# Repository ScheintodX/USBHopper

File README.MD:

#USB-Hopper

*The swiss army knife for working with microcontrollers*

##Features

* Serial interface using a FT232R
* 3 Voltages Powersupply using efficient DC-DC Buck converters:
** 5V directly from USB Bus (500mA)
** 3.3V 600mA
** 1.8V 600mA
** USB suspend supported
** not usable for heating coffee, sorry!
* USB-A Connector (no stupid cables)
* IO voltages selectable via jumper
* Sense / PWR / RX / TX LEDs
* All 4 Leds are multipurpose usable as poor mans osciloscope
* RS485 on board
* multiple comfortable headers
* cool pcb layout with sublimal messages (yea, you can call 2pt fonts sublimal ;)

##Usage Scenarios

* directly connect ESP8266 mcus to power and program them
* connect arduino boards and use the leds to show pins switching
* use rs485 to debug housebus installations or transmit data over long distances

##Errata

* RS485 termination is wrong

##Missing Features

* Additional circuity for programming esp8266 supporting RESET
* Use KiCAD instead of Eagle
* Better isolation of Sense pins
* JTAG is not working well with FT232R and so didn't manage to get in.

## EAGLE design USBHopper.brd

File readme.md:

#USB-Hopper

*The swiss army knife for working with microcontrollers*

##Features

* Serial interface using a FT232R
* 3 Voltages Powersupply using efficient DC-DC Buck converters:
** 5V directly from USB Bus (500mA)
** 3.3V 600mA
** 1.8V 600mA
** USB suspend supported
** not usable for heating coffee, sorry!
* USB-A Connector (no stupid cables)
* IO voltages selectable via jumper
* Sense / PWR / RX / TX LEDs
* All 4 Leds are multipurpose usable as poor mans osciloscope
* RS485 on board
* multiple comfortable headers
* cool pcb layout with sublimal messages (yea, you can call 2pt fonts sublimal ;)
* different assembly options using less voltages or other voltages, 

##Usage Scenarios

* directly connect ESP8266 mcus to power and program them
* connect arduino boards and use the leds to show pins switching
* use rs485 to debug housebus installations or transmit data over long distances

##Errata

** RN4604 IC must be mounted 180° rotated! **

* RS485 termination is wrong

* USB-Power supply may need less parts

##Missing Features

* Additional circuity for programming esp8266 supporting RESET
* Use KiCAD instead of Eagle
* Better isolation of Sense pins
* JTAG is not working well with FT232R and so didn't manage to get in.
* Make RE/DI controllable by FTDI pins
* Put RTS/DTR on pads (not only pins because they are usefull for esp programming)
* Make external power switchable via some signal lines / jumpers / both

#Files:

* *.brd, *.sch: eagle board and schema files
* *.BOM: Bill of Materials (text)
* parts.ods: Unfinished spreadsheet with incomplete list of parts and where to buy them and what they may have costed a long long time ago.

#Make compile

* Start with the biggest IC: the FTDI chip. There are multiple ways how you can get it on the pcb. In my optinion this is the easiest one: Put as little solder as possible on each pad. Now apply flux from a pen. Place the IC exactly on the pads and using a knife tip on the soldering iron go across the legs. Check e.g. using your mobile and some magnifing app.

* Now solder the small ics like the DC-DC converters, the mosfet and the transistor arrays. Here it works best first putting solder on *one* pad, placing the ic then soldering that one leg. Now the IC can't move anymore and you can solder the other legs easily.

* Then its time for the resistors and capacitors. Apply the same procedure as with the small ICs. I like using my fingernails to hold them while soldering but you can use tweezers, of cause.

* Now put on the remaining stuff. The usb connector and the pin header come last because they go though the pcb so that it can't lay flat anymore which would have been a major anoyance while mounting the other parts.

* finally connect the solder bridges apropriately.

#Brides/Jumpers

A. Main Power Supply jumper:

This one controls the power supply for the ftdi io pins and most of the header pins. It can have 4 settings: 5V, 3.3V FT generated, 3.3V Buck generated and 1.8V. 

B. Power LED Jumper + additional Sense pin

Can be used to disconnect the (blue) power led and use it as additional sense pin.

C. Connect RO / DI Pins of RS485 to Rx/Tx of the FT

D. Sense pin. Controls the (red) sense led.

E. Two more sense pins which can controll the Rx/Tx Leds

F. Select supply voltage to the RS485 Transceiver. Depends on the Transceiver used. Normally 3.3V.

G. Connect DE/RE Pins of the transceiver to Vcc/GND. You normally want to do this.

H. Either connect the Tx/Rx LEDS directly to the FT Led pins (jumper closed) or via transistor to the Tx/Rx Lines (jumper open but transistor arrays on the board.)

K. Not really good termination settings.

# Config

The FT232R has many config options. Use the "FT_Prog" utility to change pin mappings and maximum power rating.

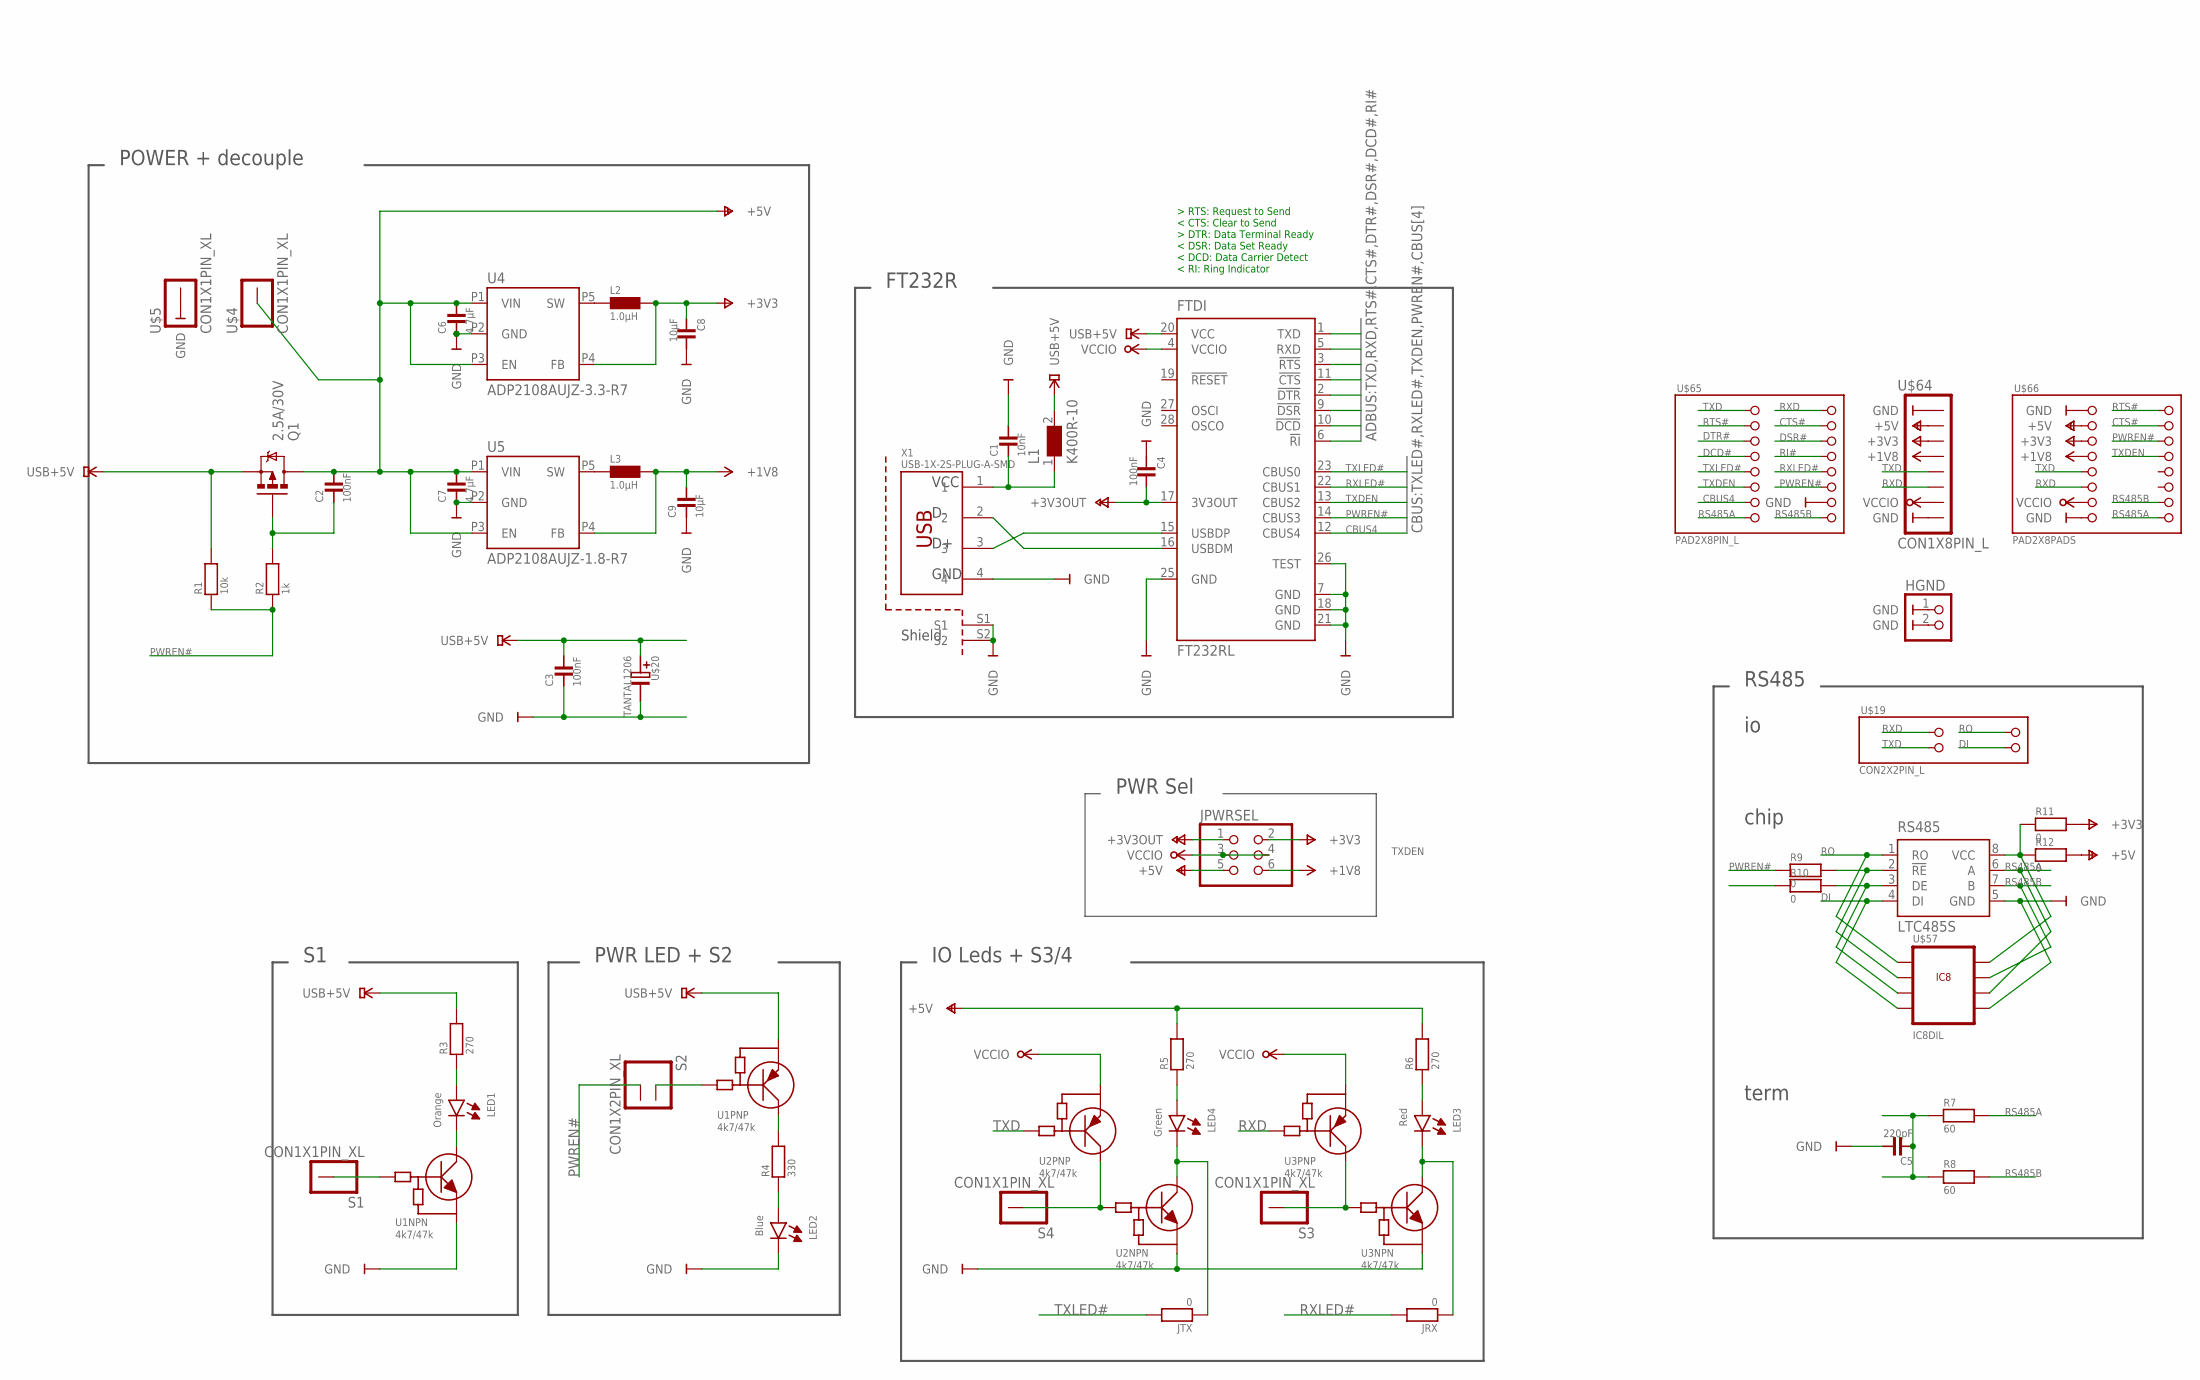
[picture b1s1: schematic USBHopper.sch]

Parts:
C1: 10nF; 0805
C2, C3, C4: 100nF; 0805
C5: 220pF; 0805
C6, C7: 4.7µF; 0805
C8, C9: 10µF; 0805
FTDI: FT232RL; SSOP28_FLO
HGND: PINHD-1X2; 1X02
JPWRSEL: PINHD-2X3; 2X03
JRX: 0; 0805_CONNECT
JTX: 0; 0805_CONNECT
L1: K400R-10; 0805
L2, L3: 1.0µH; 0806
LED1: Orange; KPT-2012-E
LED2: Blue; KPT-2012-E
LED3: Red; KPT-2012-E
LED4: Green; KPT-2012-E
Q1: 2.5A/30V; SOT23-3
R1: 10k; 0805
R2: 1k; 0805
R3, R5, R6: 270; 0805
R4: 330; 0805
R7: 60; 0805
R8: 60; 0805_CONNECT
R9, R10, R11, R12: 0; 0805_CONNECT
RS485: LTC485S; SOIC8
S1, S3, S4: CON1X1PIN_XL; 1X1PINS
S2: CON1X2PIN_XL; 1X2PINS
U1, U2, U3: 4k7/47k; SOT-457
U4: ADP2108AUJZ-3.3-R7; SOT23
U5: ADP2108AUJZ-1.8-R7; SOT23
U$4, U$5: CON1X1PIN_XL; 1X1PINS
U$19: CON2X2PIN_L; 2X2PINS_L
U$20: TANTAL1206; 1206
U$57: IC8DIL; DIL8
U$64: CON1X8PIN_L; 1X8PINS_L
U$65: PAD2X8PIN_L; 2X8PINS_L
U$66: PAD2X8PADS; 2X8PADS
X1: USB-1X-2S-PLUG-A-SMD; USB-PLUG-A-SMD-2S

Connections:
+1V8: C9.P$2, JPWRSEL.6, L3.P$1, U5.P4 (FB), U$64.P$4, U$66.P$7
+3V3: C8.P$1, JPWRSEL.2, L2.P$1, R11.P$2, U4.P4 (FB), U$64.P$3, U$66.P$5
+3V3OUT: C4.P$2, FTDI.17 (3V3OUT), JPWRSEL.1
+5V: C2.P$2, C6.P$2, C7.P$2, JPWRSEL.5, Q1.3 (D), R5.P$2, R6.P$2, R12.P$2, U4.P1 (VIN), U4.P3 (EN), U5.P1 (VIN), U5.P3 (EN), U$4.P$1, U$64.P$2, U$66.P$3
CBUS4: FTDI.12 (CBUS4), U$65.P$13
CTS#: FTDI.11 (!CTS), U$65.P$4, U$66.P$4
DCD#: FTDI.10 (!DCD), U$65.P$7
DE: R10.P$2, RS485.3 (DE), U$57.P$3
DI: RS485.4 (DI), U$19.P$4, U$57.P$4
DSR#: FTDI.9 (!DSR), U$65.P$6
DTR#: FTDI.2 (!DTR), U$65.P$5
GND: C1.P$2, C3.P$1, C4.P$1, C5.P$2, C6.P$1, C7.P$1, C8.P$2, C9.P$1, FTDI.7 (GND), FTDI.18 (GND), FTDI.21 (GND), FTDI.25 (GND), FTDI.26 (TEST), HGND.1, HGND.2, LED2.2, RS485.5 (GND), U1.P$1 (E), U2.P$1 (E), U3.P$1 (E), U4.P2 (GND), U5.P2 (GND), U$5.P$1, U$20.P$2, U$57.P$5, U$64.P$1, U$64.P$8, U$65.P$14, U$66.P$1, U$66.P$15, X1.4, X1.S1, X1.S2
unnamed: LED2.1, R4.P$1
unnamed: LED1.1, R3.P$1
unnamed: C1.P$1, L1.1, X1.1
unnamed: L2.P$2, U4.P5 (SW)
unnamed: JRX.P$1, LED3.2, U3.P$6 (C)
unnamed: L3.P$2, U5.P5 (SW)
unnamed: C5.P$1, R7.P$1, R8.P$1
unnamed: R11.P$1, R12.P$1, RS485.8 (VCC), U$57.P$8
unnamed: JTX.P$1, LED4.2, U2.P$6 (C)
unnamed: LED4.1, R5.P$1
unnamed: LED3.1, R6.P$1
unnamed: R4.P$2, U1.P$3 (C)
unnamed: S2.P$1, U1.P$5 (B)
unnamed: LED1.2, U1.P$6 (C)
PWREN: C2.P$1, Q1.1 (G), R2.P$2
PWREN#: FTDI.14 (CBUS3), R1.P$1, R2.P$1, R9.P$1, S2.P$2, U$65.P$12, U$66.P$6
RE#: R9.P$2, RS485.2 (!RE), U$57.P$2
RI#: FTDI.6 (!RI), U$65.P$8
RO: RS485.1 (RO), U$19.P$2, U$57.P$1
RS485A: R7.P$2, RS485.6 (A), U$57.P$6, U$65.P$15, U$66.P$16
RS485B: R8.P$2, RS485.7 (B), U$57.P$7, U$65.P$16, U$66.P$14
RTS#: FTDI.3 (!RTS), U$65.P$3, U$66.P$2
RXD: FTDI.5 (RXD), U3.P$5 (B), U$19.P$1, U$64.P$6, U$65.P$2, U$66.P$11
RXLED#: FTDI.22 (CBUS1), JRX.P$2, U$65.P$10
SEN3: S4.P$1, U2.P$2 (B), U2.P$3 (C)
SEN4: S3.P$1, U3.P$2 (B), U3.P$3 (C)
SENSE: S1.P$1, U1.P$2 (B)
TXD: FTDI.1 (TXD), U2.P$5 (B), U$19.P$3, U$64.P$5, U$65.P$1, U$66.P$9
TXDEN: FTDI.13 (CBUS2), R10.P$1, U$65.P$11, U$66.P$8
TXLED#: FTDI.23 (CBUS0), JTX.P$2, U$65.P$9
USB+5V: C3.P$2, FTDI.20 (VCC), L1.2, Q1.2 (S), R1.P$2, R3.P$2, U1.P$4 (E), U$20.P$1
USBDM: FTDI.16 (USBDM), X1.2
USBDP: FTDI.15 (USBDP), X1.3
VCCIO: FTDI.4 (VCCIO), JPWRSEL.3, JPWRSEL.4, U2.P$4 (E), U3.P$4 (E), U$64.P$7, U$66.P$13

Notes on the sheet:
RS485
chip
term
IO Leds + S3/4
PWR LED + S2
PWR Sel
FT232R
POWER + decouple

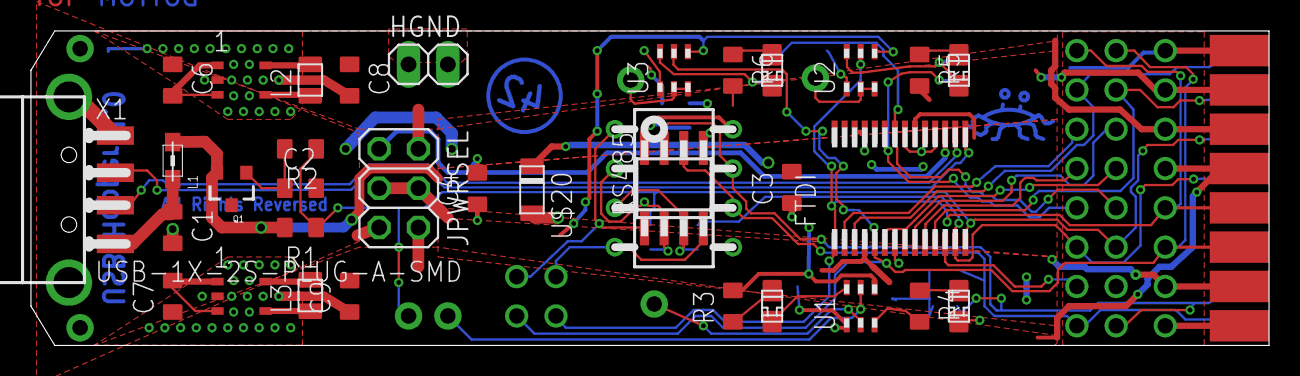
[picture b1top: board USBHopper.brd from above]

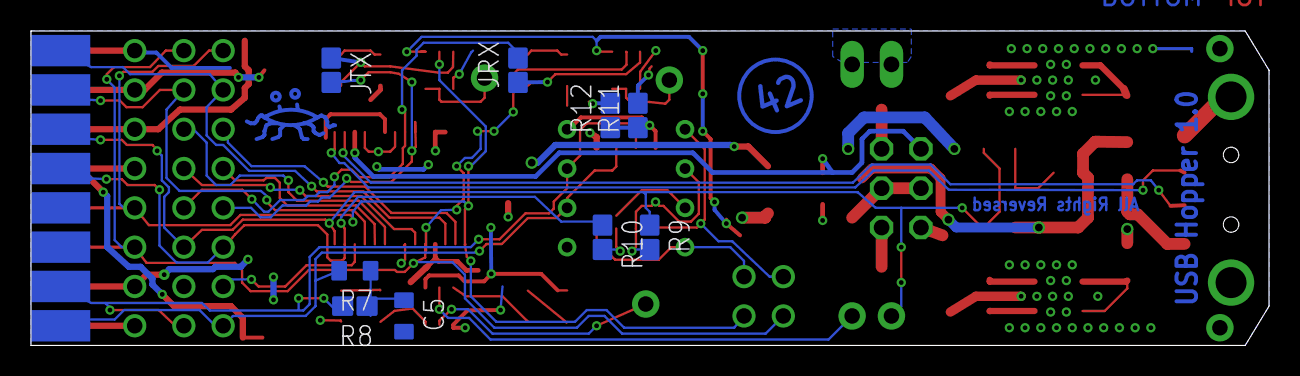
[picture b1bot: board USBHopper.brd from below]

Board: 2 copper layers, 80.0 x 20.3 mm, 53 parts (9 on the bottom side), 46 nets.

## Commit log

2015-03-01 Init checkin
2015-03-01 LED Steuerung via RN4904
2015-03-02 pnp/npn package groesser. strom schaltung gefummele.
2015-03-09 weiter pwren, leds...
2015-03-09 +5V->USB+5V bei sense
2015-03-11 Viel Layout
2015-03-11 Layout fertig. Logo!
2015-03-11 small design fixes
2015-03-11 Layout png
2015-03-11 readme angelegt
2015-03-11 LED beschriftungen
2015-03-14 The downside is the upside.
2015-03-17 Bugfixes. Pad auf GND.
2016-05-31 V1.0
2016-05-31 readme
2016-05-31 More docs
2016-05-31 mehr bilder
2016-05-31 more pics
2016-05-31 feature
2016-06-01 ftprog
2016-06-12 More featurerequests

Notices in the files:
parts and their libraries:
SparkFun-DiscreteSemi: Licensing: Creative Commons ShareAlike 4.0 International - https://creativecommons.org/licenses/by-sa/4.0
wuerth_elektronik: Copyright: Würth Elektronik
